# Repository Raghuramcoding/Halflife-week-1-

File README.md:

This is my week 1 starbie project for the half-life event, Image I got from the simulator.html file in firmware

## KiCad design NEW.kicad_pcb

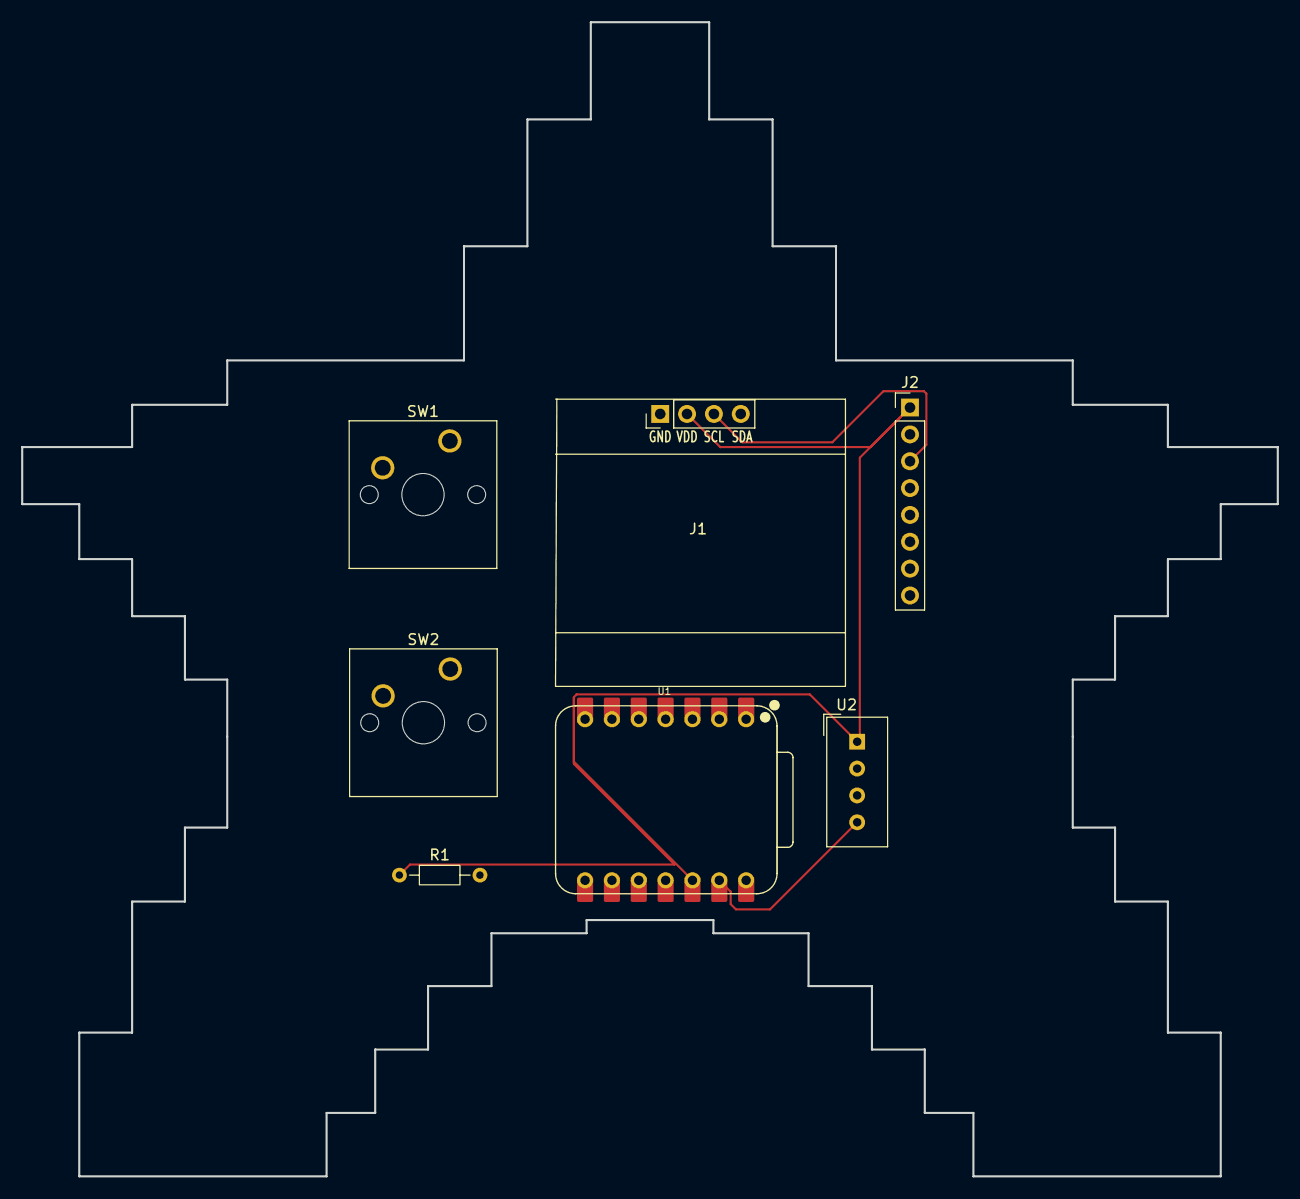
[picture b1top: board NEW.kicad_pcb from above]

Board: 2 copper layers, 118.8 x 109.2 mm, 7 parts (0 on the bottom side), 3 nets.

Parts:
J1: Conn_01x04_Pin; Display_128x64_096_I2C
J2: Conn_01x08_Pin; PinHeader_1x08_P2.54mm_Vertical
R1: 10k; R_Axial_DIN0204_L3.6mm_D1.6mm_P7.62mm_Horizontal
SW1, SW2: SW_Push; SW_Cherry_MX_1.00u_PCB
U1: XIAO-ESP32-C3-SMD; XIAO-ESP32-C6-DIP
U2: DHT11; Aosong_DHT11_5.5x12.0_P2.54mm

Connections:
+3.3V: J1.2, J2.1, R1.1, U1.12 (3V3_OUT), U2.1 (VDD)
/SCL: J1.3, J2.3
GND: J1.1, SW1.2 (2_2), SW2.2 (2_2), U1.13 (GND), U2.4 (GND)
